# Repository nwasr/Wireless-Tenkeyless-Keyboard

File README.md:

# **Wireless-Tenkeyless-Keyboard**

A compact wireless mechanical keyboard designed using the **ESP32-WROOM-S3** module. This project was developed as part of academic coursework.

> **Disclaimer:**  
> This design has not been fabricated or tested on hardware. Use at your own risk.

---

## **Keyboard Layout**

- Designed using [Keyboard Layout Editor](http://www.keyboard-layout-editor.com).
- Layout file: [layout.json](kle_files/keyboard-layout.json)
- Visual preview:

---

## **Schematic Overview**

The design follows a modular, hierarchical schematic structure:
- Root (page 1)
  - Block Level Architecture (page 2)
    - USB C (page 3)
    - MCP73871 (page 4)
    - LDO (page 5)
    - MCU (ESP32-WROOM-S3) (page 6)
    - Keyboard Matrix (page 7)

Full schematic: [schematic.pdf](schematic.pdf)

---

## **PCB Design**

---

## **Case Design**

- TODO

---

## **EMI Considerations**

- TODO
---

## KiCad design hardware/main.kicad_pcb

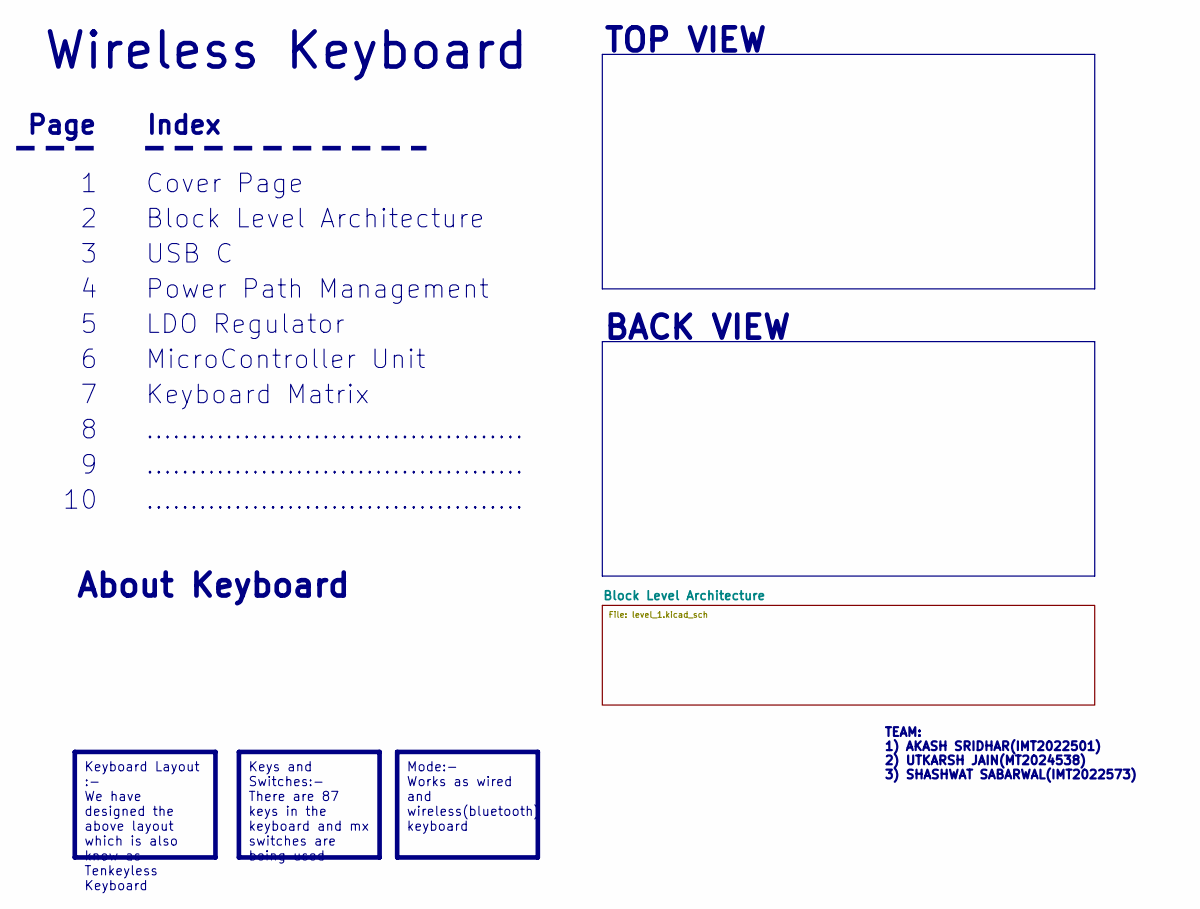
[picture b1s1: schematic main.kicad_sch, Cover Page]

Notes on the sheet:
BACK VIEW
TOP VIEW
...........................................
Index
Page
Power Path Management
TEAM: 1) AKASH SRIDHAR(IMT2022501) 2) UTKARSH JAIN(MT2024538) 3) SHASHWAT SABARWAL(IMT2022573)
LDO Regulator
Wireless Keyboard
MicroController Unit
Block Level Architecture
Cover Page
USB C
About Keyboard
Keyboard Matrix
Mode:- Works as wired and wireless(bluetooth) keyboard
Keyboard Layout :- We have designed the above layout which is also know as Tenkeyless Keyboard
Keys and Switches:- There are 87 keys in the keyboard and mx switches are being used

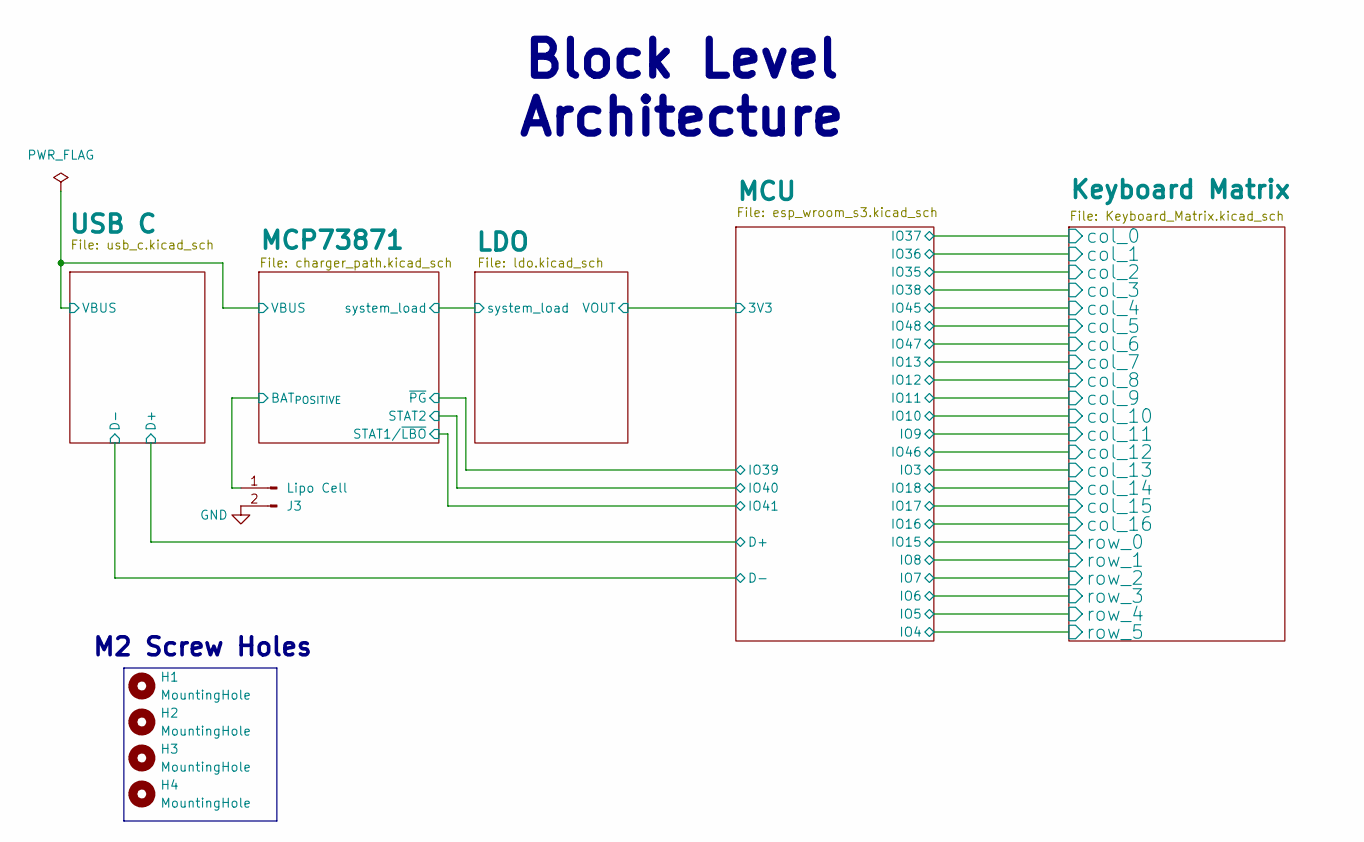
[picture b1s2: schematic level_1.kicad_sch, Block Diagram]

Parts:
H1, H2, H3, H4: MountingHole; MountingHole_2.2mm_M2
J3: Lipo Cell; JST_PH_S2B-PH-K_1x02_P2.00mm_Horizontal

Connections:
GND: J3.2; also elsewhere on the board

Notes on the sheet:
M2 Screw Holes
Block Level Architecture

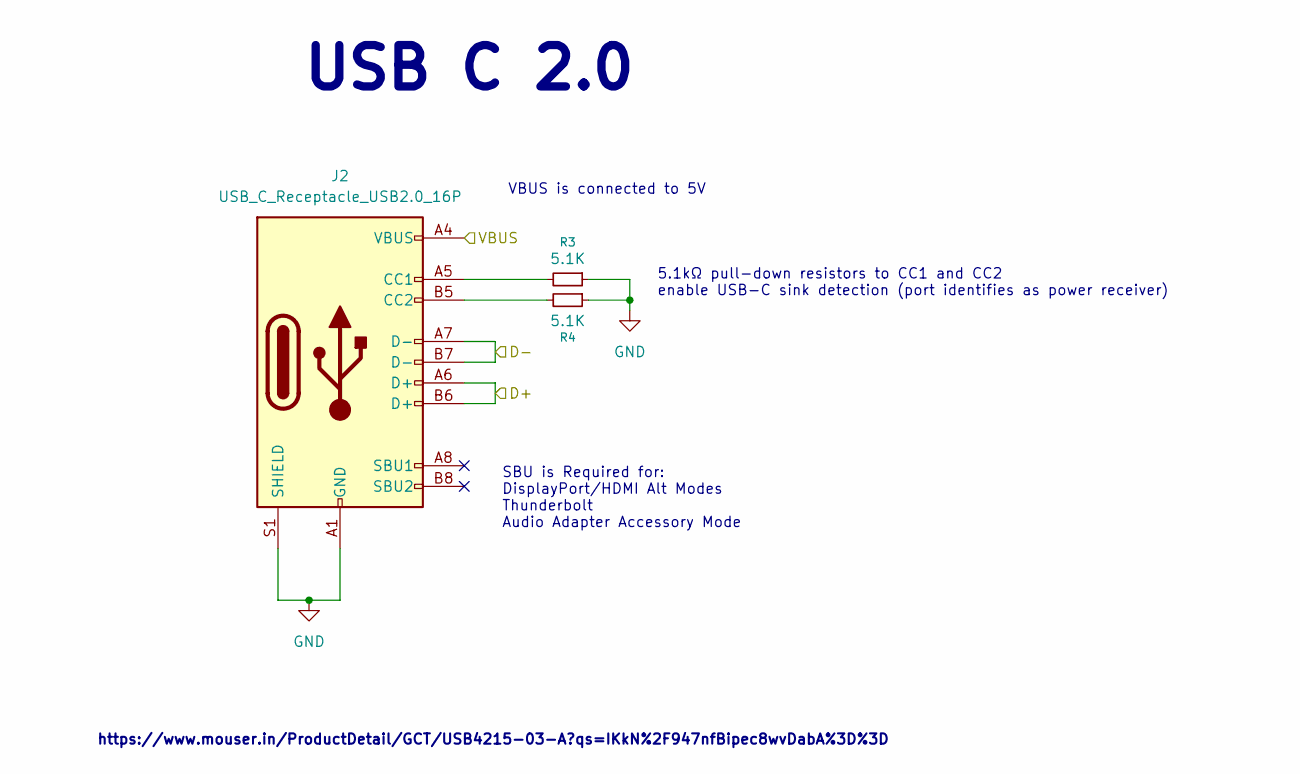
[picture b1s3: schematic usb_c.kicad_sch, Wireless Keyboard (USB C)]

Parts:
J2: USB_C_Receptacle_USB2.0_16P; USB_C_Receptacle_GCT_USB4105-xx-A_16P_TopMnt_Horizontal
R3, R4: 5.1K; R_0603_1608Metric

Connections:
/Level 1 Schematic/MCU/D+: J2.A6 (D+), J2.B6 (D+); also elsewhere on the board
/Level 1 Schematic/MCU/D-: J2.A7 (D-), J2.B7 (D-); also elsewhere on the board
GND: J2.A1 (GND), J2.A12 (GND), J2.B1 (GND), J2.B12 (GND), J2.S1 (SHIELD), R3.1, R4.1; also elsewhere on the board
unnamed: J2.A5 (CC1), R3.2
unnamed: J2.B5 (CC2), R4.2

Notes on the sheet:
VBUS is connected to 5V
5.1kΩ pull-down resistors to CC1 and CC2 enable USB-C sink detection (port identifies as power receiver)
SBU is Required for: DisplayPort/HDMI Alt Modes Thunderbolt Audio Adapter Accessory Mode
https://www.mouser.in/ProductDetail/GCT/USB4215-03-A?qs=IKkN%2F947nfBipec8wvDabA%3D%3D
USB C 2.0

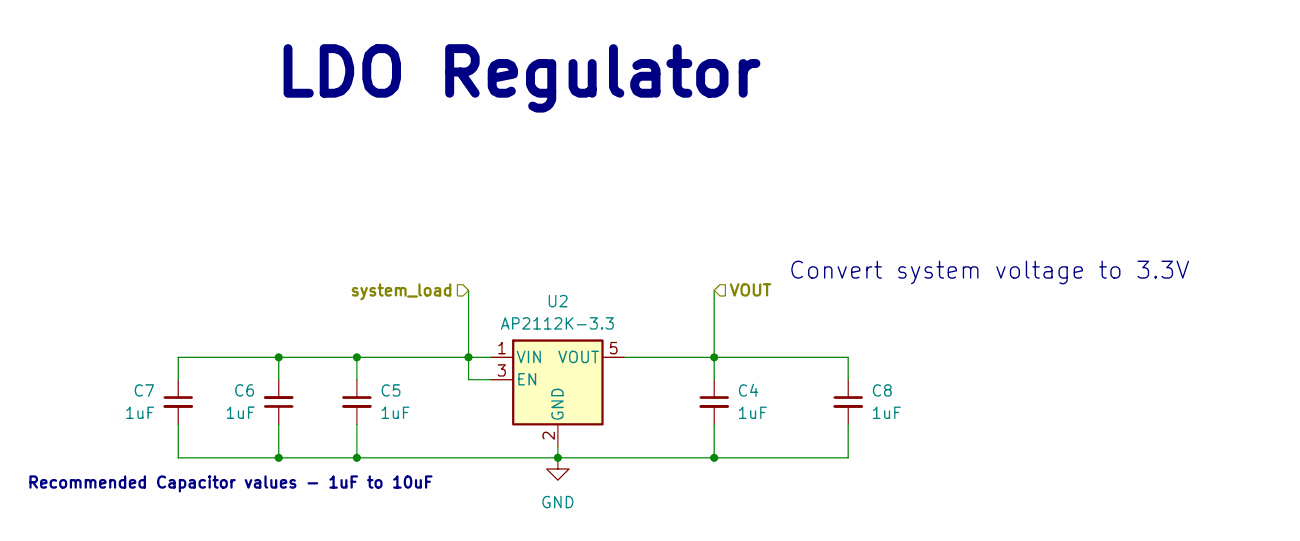
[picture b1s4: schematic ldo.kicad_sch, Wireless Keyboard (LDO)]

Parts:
C4, C5, C6, C7, C8: 1uF; C_0603_1608Metric
U2: AP2112K-3.3; SOT-23-5

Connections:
/Level 1 Schematic/LDO/VOUT: C4.1, C8.1, U2.5 (VOUT); also elsewhere on the board
/Level 1 Schematic/LDO/system_load: C5.1, C6.2, C7.1, U2.1 (VIN), U2.3 (EN); also elsewhere on the board
GND: C4.2, C5.2, C6.1, C7.2, C8.2, U2.2 (GND); also elsewhere on the board

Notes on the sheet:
Convert system voltage to 3.3V
Recommended Capacitor values - 1uF to 10uF
LDO Regulator

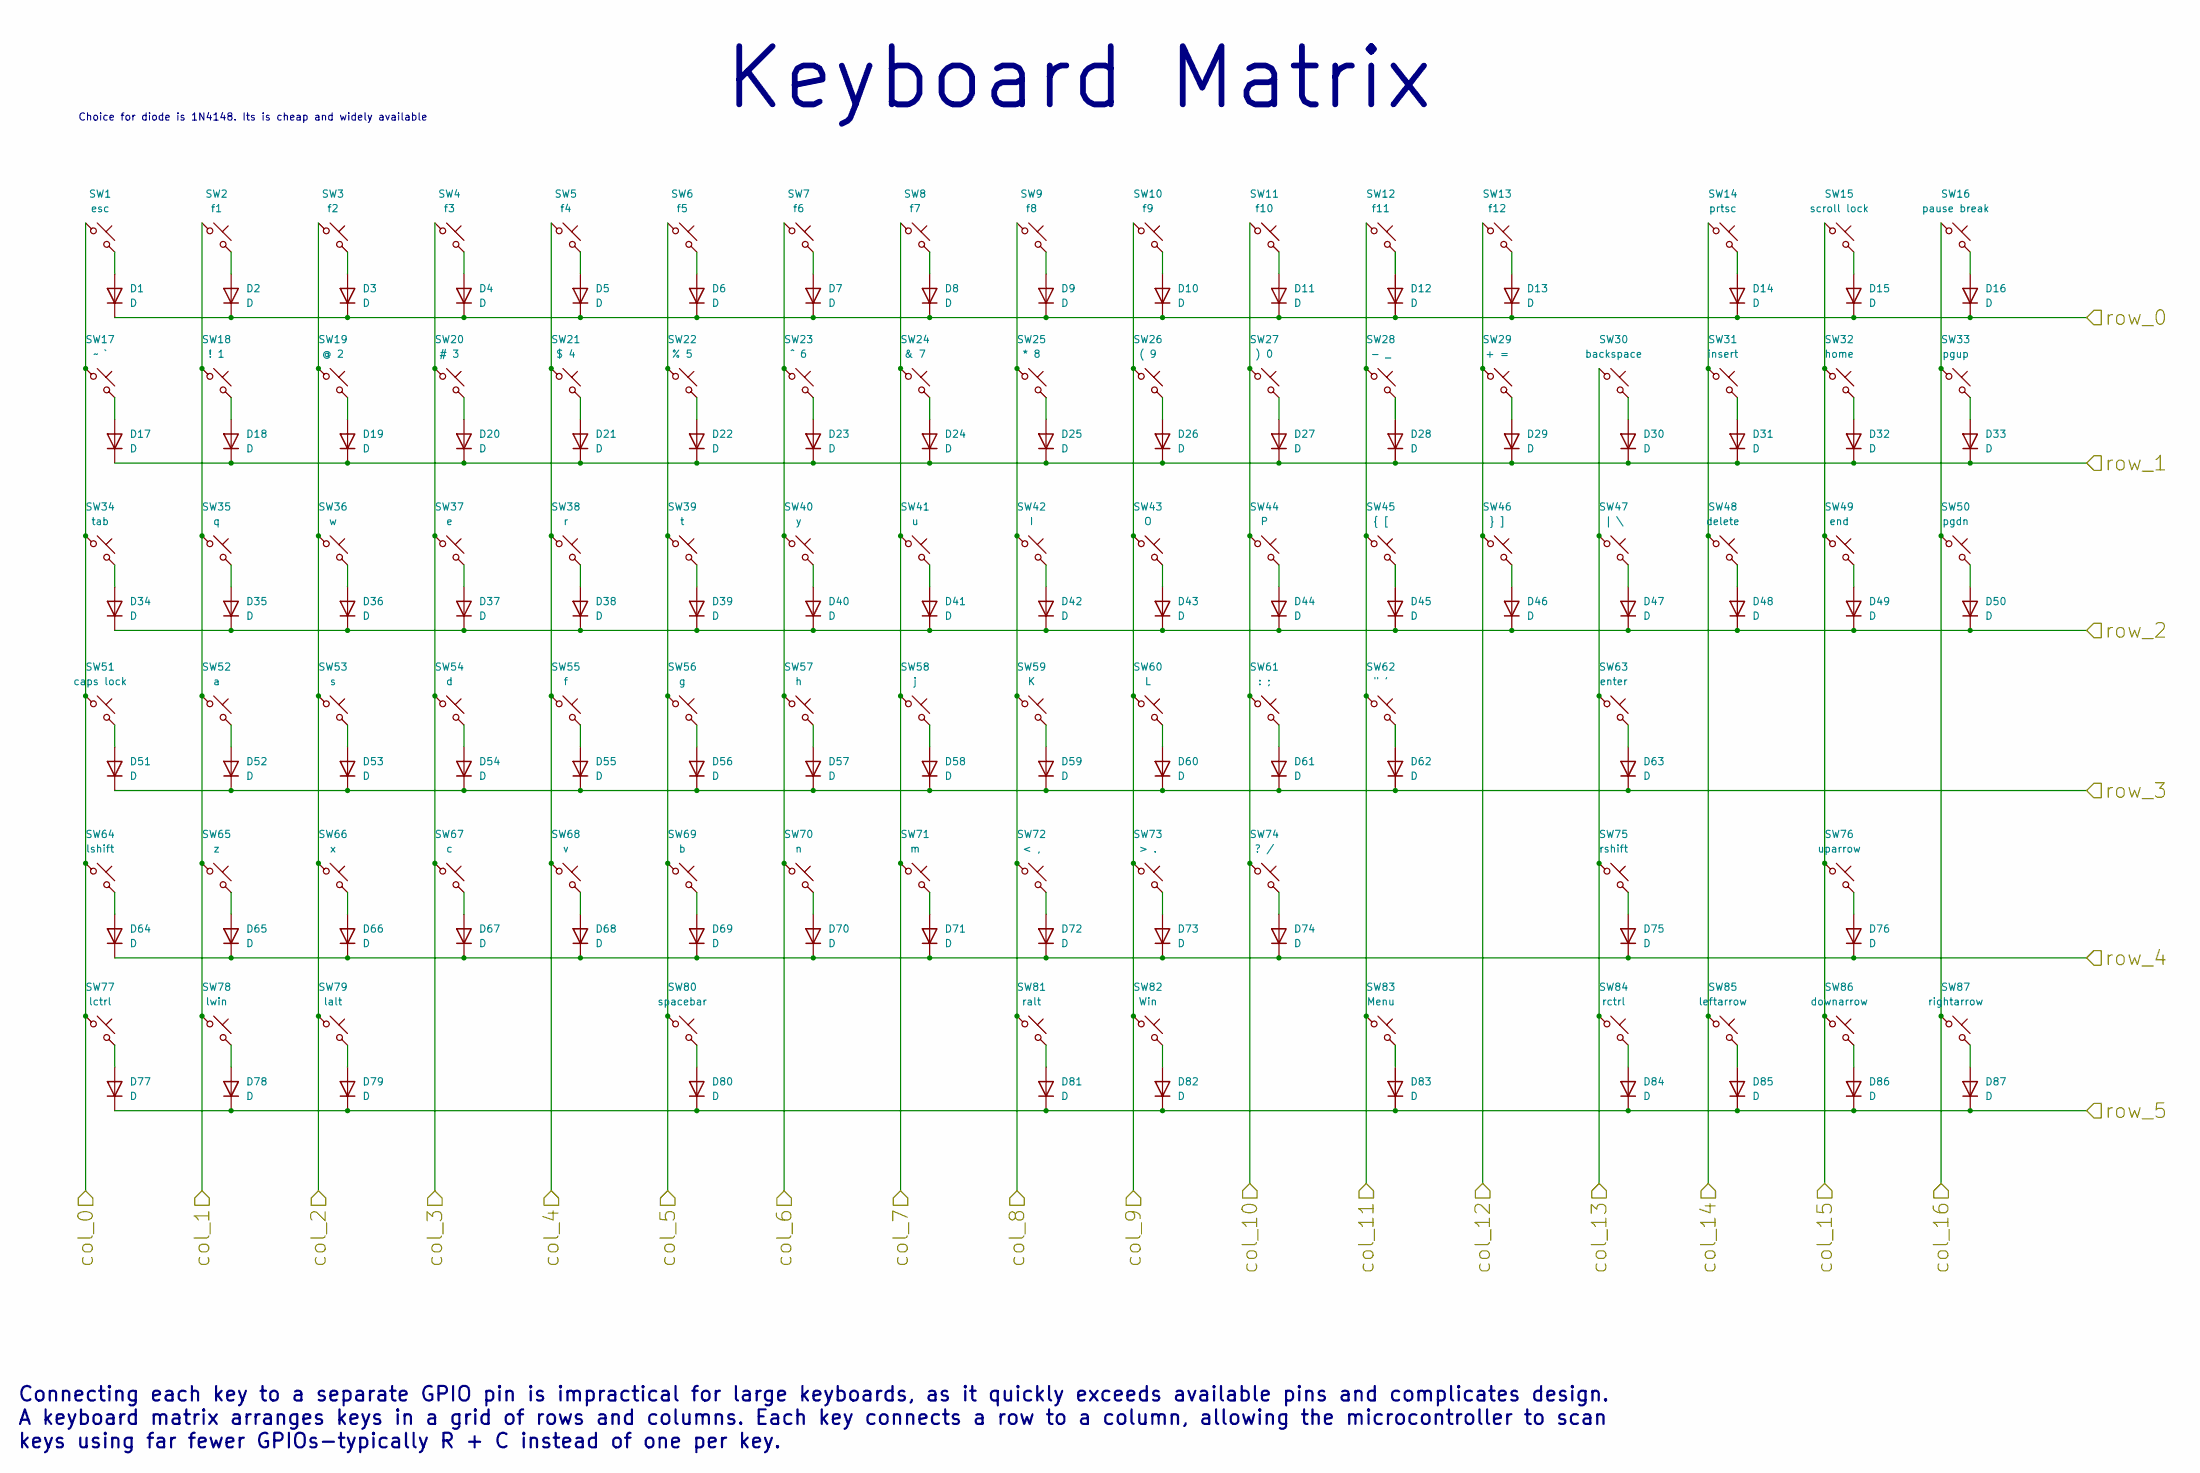
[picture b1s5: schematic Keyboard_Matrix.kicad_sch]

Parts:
D1, D2, D3, D4, D5, D6, D7, D8, D9, D10, D11, D12, D13, D14, D15, D16, D17, D18, D19, D20, D21, D22, D23, D24, D25, D26, D27, D28, D29, D30, D31, D32, D33, D34, D35, D36, D37, D38, D39, D40, D41, D42, D43, D44, D45, D46, D47, D48, D49, D50, D51, D52, D53, D54, D55, D56, D57, D58, D59, D60, D61, D62, D63, D64, D65, D66, D67, D68, D69, D70, D71, D72, D73, D74, D75, D76, D77, D78, D79, D80, D81, D82, D83, D84, D85, D86, D87: D; D_SOD-123
SW1: esc; MX_PCB_1.00u
SW2: f1; MX_PCB_1.00u
SW3: f2; MX_PCB_1.00u
SW4: f3; MX_PCB_1.00u
SW5: f4; MX_PCB_1.00u
SW6: f5; MX_PCB_1.00u
SW7: f6; MX_PCB_1.00u
SW8: f7; MX_PCB_1.00u
SW9: f8; MX_PCB_1.00u
SW10: f9; MX_PCB_1.00u
SW11: f10; MX_PCB_1.00u
SW12: f11; MX_PCB_1.00u
SW13: f12; MX_PCB_1.00u
SW14: prtsc; MX_PCB_1.00u
SW15: scroll lock; MX_PCB_1.00u
SW16: pause break; MX_PCB_1.00u
SW17: ~ `; MX_PCB_1.00u
SW18: ! 1; MX_PCB_1.00u
SW19: @ 2; MX_PCB_1.00u
SW20: # 3; MX_PCB_1.00u
SW21: $ 4; MX_PCB_1.00u
SW22: % 5; MX_PCB_1.00u
SW23: ^ 6; MX_PCB_1.00u
SW24: & 7; MX_PCB_1.00u
SW25: * 8; MX_PCB_1.00u
SW26: ( 9; MX_PCB_1.00u
SW27: ) 0; MX_PCB_1.00u
SW28: - _; MX_PCB_1.00u
SW29: + =; MX_PCB_1.00u
SW30: backspace; MX_PCB_2.00u
SW31: insert; MX_PCB_1.00u
SW32: home; MX_PCB_1.00u
SW33: pgup; MX_PCB_1.00u
SW34: tab; MX_PCB_1.50u
SW35: q; MX_PCB_1.00u
SW36: w; MX_PCB_1.00u
SW37: e; MX_PCB_1.00u
SW38: r; MX_PCB_1.00u
SW39: t; MX_PCB_1.00u
SW40: y; MX_PCB_1.00u
SW41: u; MX_PCB_1.00u
SW42: I; MX_PCB_1.00u
SW43: O; MX_PCB_1.00u
SW44: P; MX_PCB_1.00u
SW45: { [; MX_PCB_1.00u
SW46: } ]; MX_PCB_1.00u
SW47: | \; MX_PCB_1.50u
SW48: delete; MX_PCB_1.00u
SW49: end; MX_PCB_1.00u
SW50: pgdn; MX_PCB_1.00u
SW51: caps lock; MX_PCB_1.00u
SW52: a; MX_PCB_1.00u
SW53: s; MX_PCB_1.00u
SW54: d; MX_PCB_1.00u
SW55: f; MX_PCB_1.00u
SW56: g; MX_PCB_1.00u
SW57: h; MX_PCB_1.00u
SW58: j; MX_PCB_1.00u
SW59: K; MX_PCB_1.00u
SW60: L; MX_PCB_1.00u
SW61: : ;; MX_PCB_1.00u
SW62: " '; MX_PCB_1.00u
SW63: enter; MX_PCB_2.25u
SW64: lshift; MX_PCB_2.25u
SW65: z; MX_PCB_1.00u
SW66: x; MX_PCB_1.00u
SW67: c; MX_PCB_1.00u
SW68: v; MX_PCB_1.00u
SW69: b; MX_PCB_1.00u
SW70: n; MX_PCB_1.00u
SW71: m; MX_PCB_1.00u
SW72: < ,; MX_PCB_1.00u
SW73: > .; MX_PCB_1.00u
SW74: ? /; MX_PCB_1.00u
SW75: rshift; MX_PCB_2.75u
SW76: uparrow; MX_PCB_1.00u
SW77: lctrl; MX_PCB_1.25u
SW78: lwin; MX_PCB_1.25u
SW79: lalt; MX_PCB_1.25u
SW80: spacebar; MX_PCB_6.25u
SW81: ralt; MX_PCB_1.25u
SW82: Win; MX_PCB_1.25u
SW83: Menu; MX_PCB_1.25u
SW84: rctrl; MX_PCB_1.25u
SW85: leftarrow; MX_PCB_1.00u
SW86: downarrow; MX_PCB_1.00u
SW87: rightarrow; MX_PCB_1.00u

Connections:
/Level 1 Schematic/Keyboard Matrix/col_0: SW1.1, SW17.1, SW34.1, SW51.1, SW64.1, SW77.1; also elsewhere on the board
/Level 1 Schematic/Keyboard Matrix/col_1: SW2.1, SW18.1, SW35.1, SW52.1, SW65.1, SW78.1; also elsewhere on the board
/Level 1 Schematic/Keyboard Matrix/col_2: SW3.1, SW19.1, SW36.1, SW53.1, SW66.1, SW79.1; also elsewhere on the board
/Level 1 Schematic/Keyboard Matrix/col_3: SW4.1, SW20.1, SW37.1, SW54.1, SW67.1; also elsewhere on the board
/Level 1 Schematic/Keyboard Matrix/col_4: SW5.1, SW21.1, SW38.1, SW55.1, SW68.1; also elsewhere on the board
/Level 1 Schematic/Keyboard Matrix/col_5: SW6.1, SW22.1, SW39.1, SW56.1, SW69.1, SW80.1; also elsewhere on the board
/Level 1 Schematic/Keyboard Matrix/col_6: SW7.1, SW23.1, SW40.1, SW57.1, SW70.1; also elsewhere on the board
/Level 1 Schematic/Keyboard Matrix/col_7: SW8.1, SW24.1, SW41.1, SW58.1, SW71.1; also elsewhere on the board
/Level 1 Schematic/Keyboard Matrix/col_8: SW9.1, SW25.1, SW42.1, SW59.1, SW72.1, SW81.1; also elsewhere on the board
/Level 1 Schematic/Keyboard Matrix/col_9: SW10.1, SW26.1, SW43.1, SW60.1, SW73.1, SW82.1; also elsewhere on the board
/Level 1 Schematic/Keyboard Matrix/col_10: SW11.1, SW27.1, SW44.1, SW61.1, SW74.1; also elsewhere on the board
/Level 1 Schematic/Keyboard Matrix/col_11: SW12.1, SW28.1, SW45.1, SW62.1, SW83.1; also elsewhere on the board
/Level 1 Schematic/Keyboard Matrix/col_12: SW13.1, SW29.1, SW46.1; also elsewhere on the board
/Level 1 Schematic/Keyboard Matrix/col_13: SW30.1, SW47.1, SW63.1, SW75.1, SW84.1; also elsewhere on the board
/Level 1 Schematic/Keyboard Matrix/col_14: SW14.1, SW31.1, SW48.1, SW85.1; also elsewhere on the board
/Level 1 Schematic/Keyboard Matrix/col_15: SW15.1, SW32.1, SW49.1, SW76.1, SW86.1; also elsewhere on the board
/Level 1 Schematic/Keyboard Matrix/col_16: SW16.1, SW33.1, SW50.1, SW87.1; also elsewhere on the board
/Level 1 Schematic/Keyboard Matrix/row_0: D1.1 (K), D2.1 (K), D3.1 (K), D4.1 (K), D5.1 (K), D6.1 (K), D7.1 (K), D8.1 (K), D9.1 (K), D10.1 (K), D11.1 (K), D12.1 (K), D13.1 (K), D14.1 (K), D15.1 (K), D16.1 (K); also elsewhere on the board
/Level 1 Schematic/Keyboard Matrix/row_1: D17.1 (K), D18.1 (K), D19.1 (K), D20.1 (K), D21.1 (K), D22.1 (K), D23.1 (K), D24.1 (K), D25.1 (K), D26.1 (K), D27.1 (K), D28.1 (K), D29.1 (K), D30.1 (K), D31.1 (K), D32.1 (K), D33.1 (K); also elsewhere on the board
/Level 1 Schematic/Keyboard Matrix/row_2: D34.1 (K), D35.1 (K), D36.1 (K), D37.1 (K), D38.1 (K), D39.1 (K), D40.1 (K), D41.1 (K), D42.1 (K), D43.1 (K), D44.1 (K), D45.1 (K), D46.1 (K), D47.1 (K), D48.1 (K), D49.1 (K), D50.1 (K); also elsewhere on the board
/Level 1 Schematic/Keyboard Matrix/row_3: D51.1 (K), D52.1 (K), D53.1 (K), D54.1 (K), D55.1 (K), D56.1 (K), D57.1 (K), D58.1 (K), D59.1 (K), D60.1 (K), D61.1 (K), D62.1 (K), D63.1 (K); also elsewhere on the board
/Level 1 Schematic/Keyboard Matrix/row_4: D64.1 (K), D65.1 (K), D66.1 (K), D67.1 (K), D68.1 (K), D69.1 (K), D70.1 (K), D71.1 (K), D72.1 (K), D73.1 (K), D74.1 (K), D75.1 (K), D76.1 (K); also elsewhere on the board
/Level 1 Schematic/Keyboard Matrix/row_5: D77.1 (K), D78.1 (K), D79.1 (K), D80.1 (K), D81.1 (K), D82.1 (K), D83.1 (K), D84.1 (K), D85.1 (K), D86.1 (K), D87.1 (K); also elsewhere on the board
unnamed: D1.2 (A), SW1.2
unnamed: D2.2 (A), SW2.2
unnamed: D3.2 (A), SW3.2
unnamed: D4.2 (A), SW4.2
unnamed: D5.2 (A), SW5.2
unnamed: D6.2 (A), SW6.2
unnamed: D7.2 (A), SW7.2
unnamed: D8.2 (A), SW8.2
unnamed: D9.2 (A), SW9.2
unnamed: D10.2 (A), SW10.2
unnamed: D11.2 (A), SW11.2
unnamed: D12.2 (A), SW12.2
unnamed: D13.2 (A), SW13.2
unnamed: D14.2 (A), SW14.2
unnamed: D15.2 (A), SW15.2
unnamed: D16.2 (A), SW16.2
unnamed: D17.2 (A), SW17.2
unnamed: D18.2 (A), SW18.2
unnamed: D19.2 (A), SW19.2
unnamed: D20.2 (A), SW20.2
unnamed: D21.2 (A), SW21.2
unnamed: D22.2 (A), SW22.2
unnamed: D23.2 (A), SW23.2
unnamed: D24.2 (A), SW24.2
unnamed: D25.2 (A), SW25.2
unnamed: D26.2 (A), SW26.2
unnamed: D27.2 (A), SW27.2
unnamed: D28.2 (A), SW28.2
unnamed: D29.2 (A), SW29.2
unnamed: D30.2 (A), SW30.2
unnamed: D31.2 (A), SW31.2
unnamed: D32.2 (A), SW32.2
unnamed: D33.2 (A), SW33.2
unnamed: D34.2 (A), SW34.2
unnamed: D35.2 (A), SW35.2
unnamed: D36.2 (A), SW36.2
unnamed: D37.2 (A), SW37.2
unnamed: D38.2 (A), SW38.2
unnamed: D39.2 (A), SW39.2
unnamed: D40.2 (A), SW40.2
unnamed: D41.2 (A), SW41.2
unnamed: D42.2 (A), SW42.2
unnamed: D43.2 (A), SW43.2
unnamed: D44.2 (A), SW44.2
unnamed: D45.2 (A), SW45.2
unnamed: D46.2 (A), SW46.2
unnamed: D47.2 (A), SW47.2
unnamed: D48.2 (A), SW48.2
unnamed: D49.2 (A), SW49.2
unnamed: D50.2 (A), SW50.2
unnamed: D51.2 (A), SW51.2
unnamed: D52.2 (A), SW52.2
unnamed: D53.2 (A), SW53.2
unnamed: D54.2 (A), SW54.2
unnamed: D55.2 (A), SW55.2
unnamed: D56.2 (A), SW56.2
unnamed: D57.2 (A), SW57.2
unnamed: D58.2 (A), SW58.2
unnamed: D59.2 (A), SW59.2
unnamed: D60.2 (A), SW60.2
unnamed: D61.2 (A), SW61.2
unnamed: D62.2 (A), SW62.2
unnamed: D63.2 (A), SW63.2
unnamed: D64.2 (A), SW64.2
unnamed: D65.2 (A), SW65.2
unnamed: D66.2 (A), SW66.2
unnamed: D67.2 (A), SW67.2
unnamed: D68.2 (A), SW68.2
unnamed: D69.2 (A), SW69.2
unnamed: D70.2 (A), SW70.2
unnamed: D71.2 (A), SW71.2
unnamed: D72.2 (A), SW72.2
unnamed: D73.2 (A), SW73.2
unnamed: D74.2 (A), SW74.2
unnamed: D75.2 (A), SW75.2
unnamed: D76.2 (A), SW76.2
unnamed: D77.2 (A), SW77.2
unnamed: D78.2 (A), SW78.2
unnamed: D79.2 (A), SW79.2
unnamed: D80.2 (A), SW80.2
unnamed: D81.2 (A), SW81.2
unnamed: D82.2 (A), SW82.2
unnamed: D83.2 (A), SW83.2
unnamed: D84.2 (A), SW84.2
unnamed: D85.2 (A), SW85.2
unnamed: D86.2 (A), SW86.2
unnamed: D87.2 (A), SW87.2

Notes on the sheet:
Choice for diode is 1N4148. Its is cheap and widely available
Connecting each key to a separate GPIO pin is impractical for large keyboards, as it quickly exceeds available pins and complicates design. A keyboard matrix arranges keys in a grid of rows and columns. Each key connects a row to a column, allowing the microcontroller to scan keys using far fewer G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
Keyboard Matrix

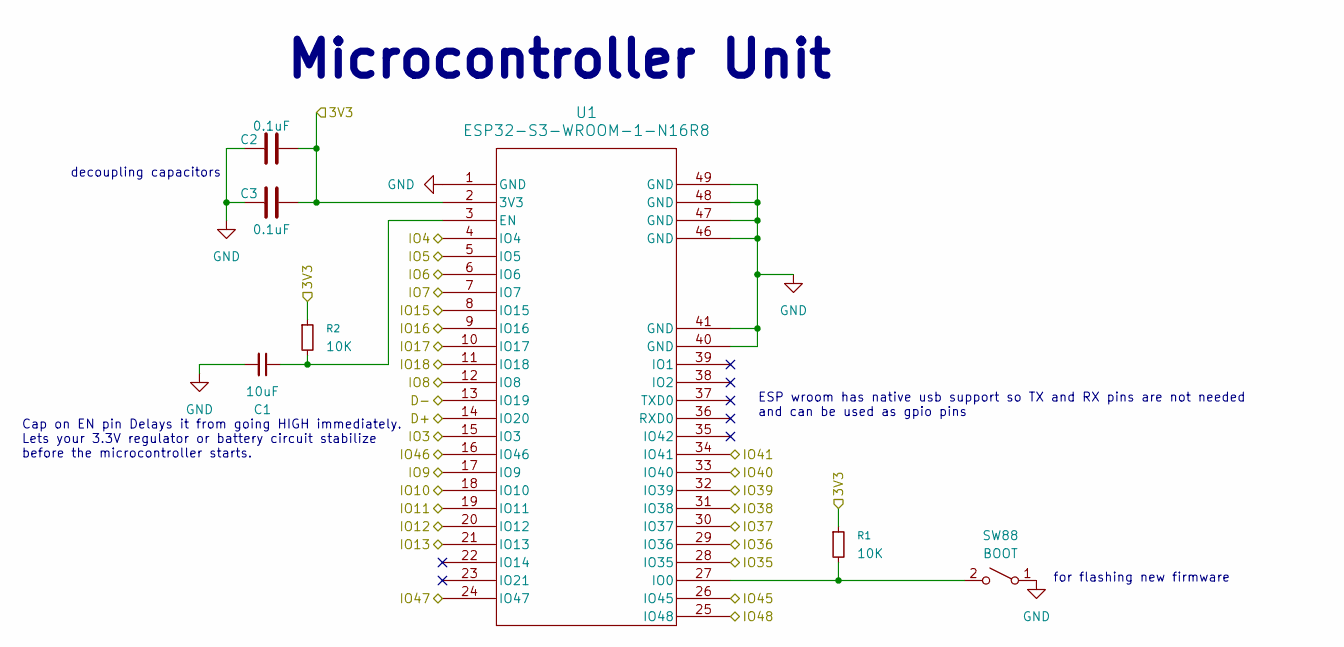
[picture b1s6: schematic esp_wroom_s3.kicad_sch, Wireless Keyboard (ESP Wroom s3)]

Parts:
C1: 10uF; C_0603_1608Metric
C2, C3: 0.1uF; C_0603_1608Metric
R1, R2: 10K; R_0603_1608Metric
SW88: BOOT; SW_SPST_PTS645
U1: ESP32-S3-WROOM-1-N16R8; ESP32-S3-WROOM-1_EXP

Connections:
/Level 1 Schematic/Keyboard Matrix/col_0: U1.30 (IO37); also elsewhere on the board
/Level 1 Schematic/Keyboard Matrix/col_1: U1.29 (IO36); also elsewhere on the board
/Level 1 Schematic/Keyboard Matrix/col_2: U1.28 (IO35); also elsewhere on the board
/Level 1 Schematic/Keyboard Matrix/col_3: U1.31 (IO38); also elsewhere on the board
/Level 1 Schematic/Keyboard Matrix/col_4: U1.26 (IO45); also elsewhere on the board
/Level 1 Schematic/Keyboard Matrix/col_5: U1.25 (IO48); also elsewhere on the board
/Level 1 Schematic/Keyboard Matrix/col_6: U1.24 (IO47); also elsewhere on the board
/Level 1 Schematic/Keyboard Matrix/col_7: U1.21 (IO13); also elsewhere on the board
/Level 1 Schematic/Keyboard Matrix/col_8: U1.20 (IO12); also elsewhere on the board
/Level 1 Schematic/Keyboard Matrix/col_9: U1.19 (IO11); also elsewhere on the board
/Level 1 Schematic/Keyboard Matrix/col_10: U1.18 (IO10); also elsewhere on the board
/Level 1 Schematic/Keyboard Matrix/col_11: U1.17 (IO9); also elsewhere on the board
/Level 1 Schematic/Keyboard Matrix/col_12: U1.16 (IO46); also elsewhere on the board
/Level 1 Schematic/Keyboard Matrix/col_13: U1.15 (IO3); also elsewhere on the board
/Level 1 Schematic/Keyboard Matrix/col_14: U1.11 (IO18); also elsewhere on the board
/Level 1 Schematic/Keyboard Matrix/col_15: U1.10 (IO17); also elsewhere on the board
/Level 1 Schematic/Keyboard Matrix/col_16: U1.9 (IO16); also elsewhere on the board
/Level 1 Schematic/Keyboard Matrix/row_0: U1.8 (IO15); also elsewhere on the board
/Level 1 Schematic/Keyboard Matrix/row_1: U1.12 (IO8); also elsewhere on the board
/Level 1 Schematic/Keyboard Matrix/row_2: U1.7 (IO7); also elsewhere on the board
/Level 1 Schematic/Keyboard Matrix/row_3: U1.6 (IO6); also elsewhere on the board
/Level 1 Schematic/Keyboard Matrix/row_4: U1.5 (IO5); also elsewhere on the board
/Level 1 Schematic/Keyboard Matrix/row_5: U1.4 (IO4); also elsewhere on the board
/Level 1 Schematic/LDO/VOUT: C2.1, C3.1, R1.1, R2.1, U1.2 (3V3); also elsewhere on the board
/Level 1 Schematic/MCP73871/STAT1/~LBO: U1.34 (IO41); also elsewhere on the board
/Level 1 Schematic/MCP73871/STAT2: U1.33 (IO40); also elsewhere on the board
/Level 1 Schematic/MCP73871/~PG: U1.32 (IO39); also elsewhere on the board
/Level 1 Schematic/MCU/D+: U1.14 (IO20); also elsewhere on the board
/Level 1 Schematic/MCU/D-: U1.13 (IO19); also elsewhere on the board
GND: C1.2, C2.2, C3.2, SW88.1 (A), U1.1 (GND), U1.40 (GND), U1.41 (GND), U1.46 (GND), U1.47 (GND), U1.48 (GND), U1.49 (GND); also elsewhere on the board
unnamed: R1.2, SW88.2 (B), U1.27 (IO0)
unnamed: C1.1, R2.2, U1.3 (EN)

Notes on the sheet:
Cap on EN pin Delays it from going HIGH immediately. Lets your 3.3V regulator or battery circuit stabilize before the microcontroller starts.
ESP wroom has native usb support so TX and RX pins are not needed and can be used as gpio pins
for flashing new firmware
decoupling capacitors
Microcontroller Unit

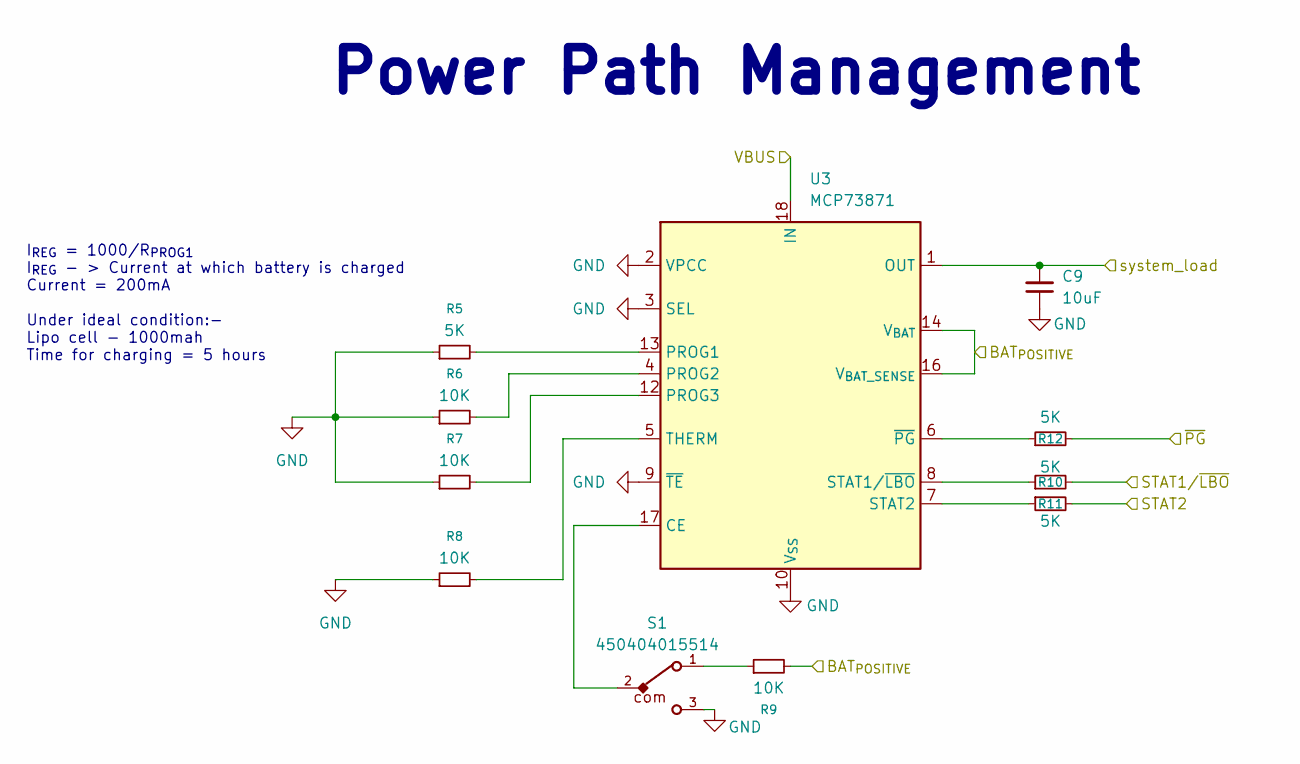
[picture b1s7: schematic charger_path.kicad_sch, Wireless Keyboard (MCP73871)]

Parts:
C9: 10uF; C_0603_1608Metric
R5, R10, R11, R12: 5K; R_0603_1608Metric
R6, R7, R8, R9: 10K; R_0603_1608Metric
S1: 450404015514; DigiKey_Part_Number 732-13665-2-ND
U3: MCP73871; QFN-20-1EP_4x4mm_P0.5mm_EP2.5x2.5mm

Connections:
/Level 1 Schematic/LDO/system_load: C9.2, U3.1 (OUT), U3.20 (OUT); also elsewhere on the board
/Level 1 Schematic/MCP73871/STAT1/~LBO: R10.1, U3.8 (STAT1/~LBO); also elsewhere on the board
/Level 1 Schematic/MCP73871/STAT2: R11.1, U3.7 (STAT2); also elsewhere on the board
/Level 1 Schematic/MCP73871/~PG: R12.1, U3.6 (~PG); also elsewhere on the board
GND: C9.1, R5.1, R6.1, R7.1, R8.1, S1.3, U3.2 (VPCC), U3.3 (SEL), U3.9 (~TE), U3.10 (V_{SS}), U3.11 (V_{SS}), U3.21 (V_{SS}); also elsewhere on the board
unnamed: R9.1, S1.1
unnamed: S1.2, U3.17 (CE)
unnamed: R5.2, U3.13 (PROG1)
unnamed: R6.2, U3.4 (PROG2)
unnamed: R7.2, U3.12 (PROG3)
unnamed: R8.2, U3.5 (THERM)

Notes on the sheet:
I_{REG} = 1000/R_{PROG1} I_{REG} - > Current at which battery is charged Current = 200mA Under ideal condition:- Lipo cell - 1000mah Time for charging = 5 hours
Power Path Management

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
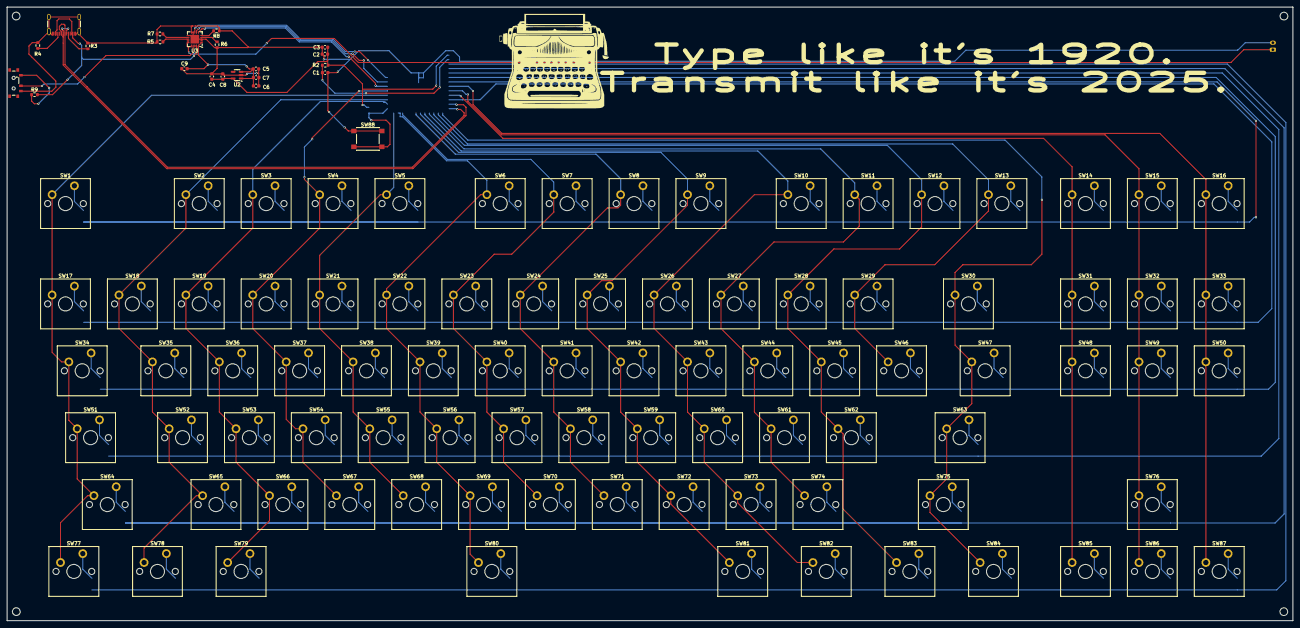
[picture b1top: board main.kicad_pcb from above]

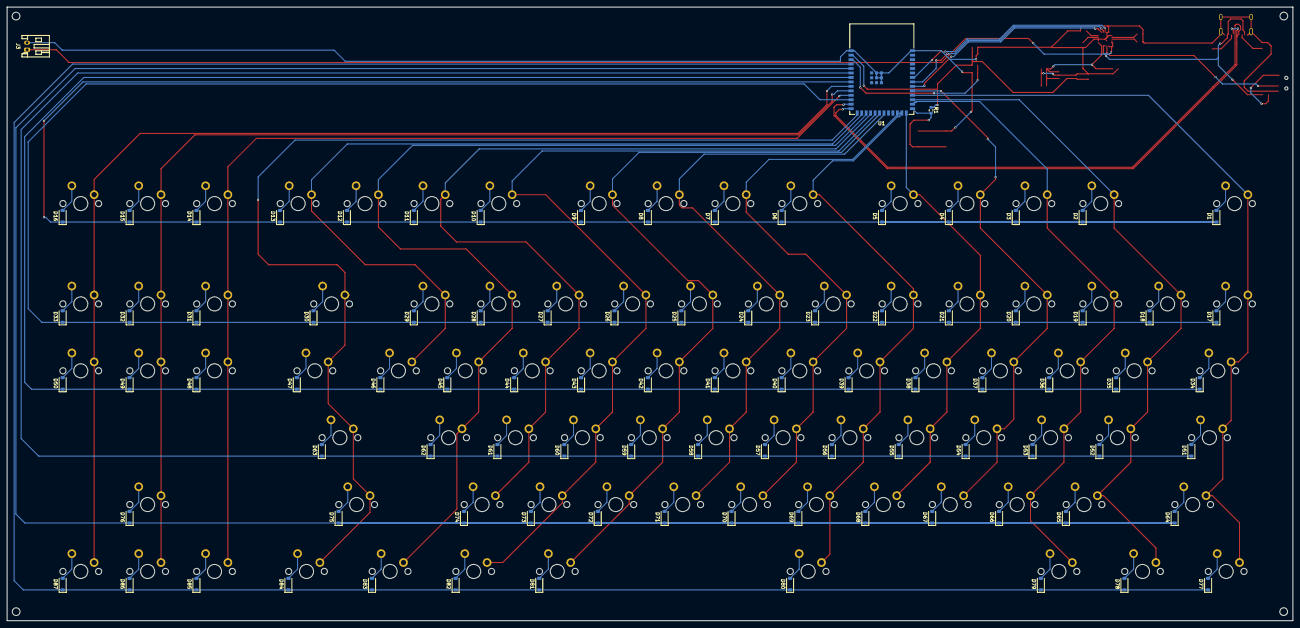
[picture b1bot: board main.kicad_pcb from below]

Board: 2 copper layers, 366.2 x 174.8 mm, 203 parts (90 on the bottom side), 130 nets.

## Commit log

2025-04-19 uploaded kle files and updated readme
2025-04-19 updated schematic section in readme
2025-04-19 updated readme and added assets
2025-04-21 added hardware files
2025-04-27 removed hardware files
